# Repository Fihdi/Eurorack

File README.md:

# Open Source Eurorack Synthesizer

Schematics and PCBs for my Eurorack modules

**2nd May 2026: UNDER CONSTRUCTION!** I am currently fixing and re-organizing every module.

The following modules are being re-worked and can be found in their own repositories:

* 30hp Drum, Hi Hat and WAV Player: [MiniDrumkit](https://github.com/Fihdi/MiniDrumkit)
* 8hp ADSR Envelope Generator: [SCULPT](https://github.com/Fihdi/SCULPT)
* 8hp Dual VCAs / Ringmodulators: [BIPO](https://github.com/Fihdi/BIPO)
* 8hp 12dB/Oct State Variable VCF: [SVF12](https://github.com/Fihdi/SVF12)
* 8hp Voltage Controlled Attack/Release and Slew Rate limiter: [VCAR](https://github.com/Fihdi/VCAR)
* 8hp VCO/LFO: [UNO](https://github.com/Fihdi/UNO)
* 6hp S&H and Random Voltage/Gate generator: [DICE](https://github.com/Fihdi/DICE)
* 6hp Wavefolder: [MWMWM](https://github.com/Fihdi/MWMWM)
* 10hp Digital FX: [DSPFX](https://github.com/Fihdi/DSP-FX32)
* 8hp Four stage Phaser: [QPOL](https://github.com/Fihdi/QPOL)
* 10hp FM-Radio: [ATS20](https://github.com/Fihdi/ATS-20-Eurorack)
* 4hp Headphone/Line-Input: [LIN](https://github.com/Fihdi/LIN)

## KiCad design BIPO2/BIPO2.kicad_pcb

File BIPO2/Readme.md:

# 8hp Dual Bipolar VCA

BIPO (short for bipolar VCA) is a dual VCA and dual ring modulator (four quadrant multiplier). The VCA outputs are mixed together, so this module can acts as a 2 channel mixer or as a crossfader. This module serves as my general purpose VCA and as a replacement for my old crossfader module.

The four quadrant multiplication is achieved by taking an attenuverter topology and replacing the potentiometer with a VCA. The VCA needs to be biased in such a way that the amplitude of the VCA output is half of the input signal at 0V. The benefit of this topology is getting two outputs simultaneously

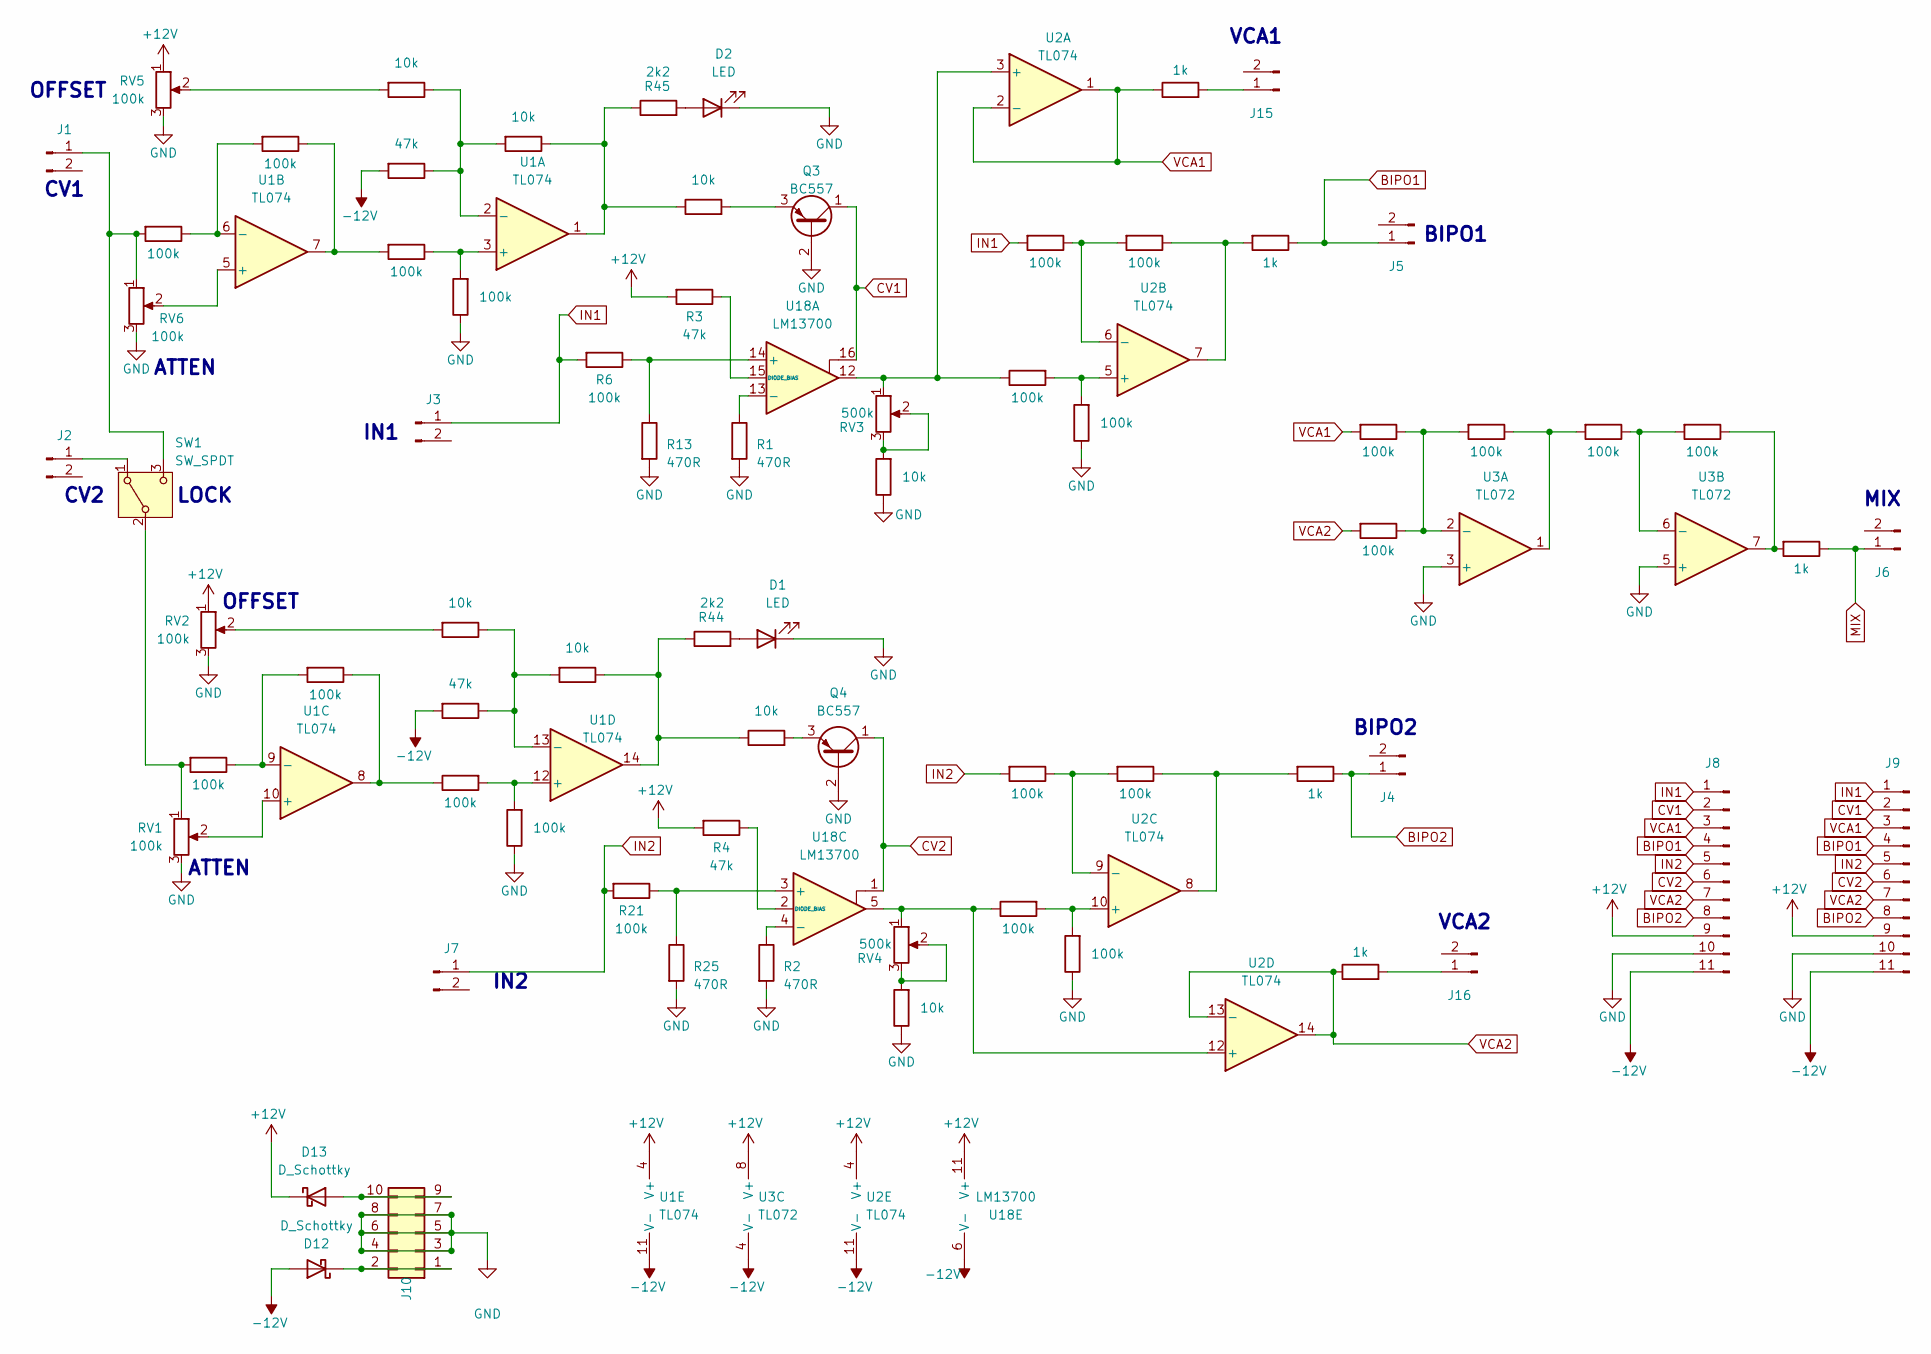
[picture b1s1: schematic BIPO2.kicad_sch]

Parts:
D1, D2: LED; LED_D3.0mm
D12, D13: D_Schottky; D_SOD-323_HandSoldering
J1, J2, J3, J4, J5, J6, J7, J15, J16: Conn_01x02_Pin; 3mm5 Mono Aux
J8, J9: Conn_01x11_Pin; PinHeader_1x11_P2.54mm_Vertical
J10: Conn_02x05_Odd_Even; IDC-Header_2x05_P2.54mm_Vertical
Q3, Q4: BC557; TO-92L_Inline_Wide
R1, R2, R13, R25: 470R; R_1206_3216Metric
R3, R4, R10, R22: 47k; R_1206_3216Metric
R5, R7, R11, R12, R20, R26, R28, R83: 10k; R_1206_3216Metric
R6, R8, R9, R14, R15, R16, R17, R18, R19, R21, R23, R24, R27, R29, R30, R31, R32, R34, R35, R38, R39, R41, R42: 100k; R_1206_3216Metric
R33, R36, R37, R40, R43: 1k; R_1206_3216Metric
R44, R45: 2k2; R_1206_3216Metric
RV1, RV2, RV5, RV6: 100k; AlpsPot_NoMountPins
RV3, RV4: 500k; Potentiometer_ACP_CA9-H5_Horizontal
SW1: SW_SPDT; Switch
U1, U2: TL074; SOIC-14_3.9x8.7mm_P1.27mm
U3: TL072; SOIC-8_3.9x4.9mm_P1.27mm
U18: LM13700; SOIC-16_3.9x9.9mm_P1.27mm

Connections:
+12V: D13.1 (K), J8.9, J9.9, R3.2, R4.2, RV2.1, RV5.1, U1.4 (V+), U2.4 (V+), U3.8 (V+), U18.11 (V+)
-12V: D12.2 (A), J8.11, J9.11, R10.2, R22.2, U1.11 (V-), U2.11 (V-), U3.4 (V-), U18.6 (V-)
BIPO1: J5.1, J8.4, J9.4, R36.1
BIPO2: J4.1, J8.8, J9.8, R33.1
CV1: J8.2, J9.2, Q3.1 (C), U18.16
CV2: J8.6, J9.6, Q4.1 (C), U18.1
GND: D1.1 (K), D2.1 (K), J8.10, J9.10, J10.3, J10.4, J10.5, J10.6, J10.7, J10.8, Q3.2 (B), Q4.2 (B), R1.2, R2.2, R5.1, R7.1, R8.1, R13.2, R24.1, R25.2, R39.1, R42.1, RV1.3, RV2.3, RV5.3, RV6.3, U3.3 (+), U3.5 (+)
IN1: J3.1, J8.1, J9.1, R6.2, R17.2
IN2: J7.1, J8.5, J9.5, R21.2, R34.2
MIX: J6.1, R37.1
unnamed: D1.2 (A), R44.2
unnamed: D2.2 (A), R45.2
unnamed: D12.1 (K), J10.1, J10.2
unnamed: D13.2 (A), J10.9, J10.10
unnamed: J1.1, R15.2, RV6.1, SW1.3 (C)
unnamed: J2.1, SW1.1 (A)
unnamed: J15.1, R40.2
unnamed: J16.1, R43.2
unnamed: Q3.3 (E), R83.2
unnamed: Q4.3 (E), R28.2
unnamed: R5.2, RV3.2, RV3.3
unnamed: R7.2, RV4.2, RV4.3
unnamed: R11.1, R45.1, R83.1, U1.1
unnamed: R12.2, RV5.2
unnamed: R9.2, R14.1, U1.7
unnamed: R16.1, R36.2, U2.7
unnamed: R19.1, R23.1, U1.8
unnamed: R20.2, RV2.2
unnamed: R26.1, R28.1, R44.1, U1.14
unnamed: R29.1, R30.2, U3.1
unnamed: R31.1, R37.2, U3.7
unnamed: R33.2, R35.1, U2.8
unnamed: R18.2, RV1.1, SW1.2 (B)
unnamed: R8.2, R9.1, U1.3 (+)
unnamed: R10.1, R11.2, R12.1, U1.2 (-)
unnamed: RV6.2, U1.5 (+)
unnamed: R14.2, R15.1, U1.6 (-)
unnamed: RV1.2, U1.10 (+)
unnamed: R18.1, R19.2, U1.9 (-)
unnamed: R23.2, R24.2, U1.12 (+)
unnamed: R20.1, R22.1, R26.2, U1.13 (-)
unnamed: R38.1, RV3.1, U2.3 (+), U18.12
unnamed: R38.2, R39.2, U2.5 (+)
unnamed: R16.2, R17.1, U2.6 (-)
unnamed: R41.2, R42.2, U2.10 (+)
unnamed: R34.1, R35.2, U2.9 (-)
unnamed: R41.1, RV4.1, U2.12 (+), U18.5
unnamed: R27.1, R29.2, R32.1, U3.2 (-)
unnamed: R30.1, R31.2, U3.6 (-)
unnamed: R6.1, R13.1, U18.14 (+)
unnamed: R1.1, U18.13 (-)
unnamed: R3.1, U18.15 (DIODE_BIAS)
unnamed: R21.1, R25.1, U18.3 (+)
unnamed: R2.1, U18.4 (-)
unnamed: R4.1, U18.2 (DIODE_BIAS)
VCA1: J8.3, J9.3, R27.2, R40.1, U2.1, U2.2 (-)
VCA2: J8.7, J9.7, R32.2, R43.1, U2.13 (-), U2.14

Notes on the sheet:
BIPO2
CV1
OFFSET
VCA1
IN2
LOCK
IN1
ATTEN
VCA2
BIPO1
MIX
CV2

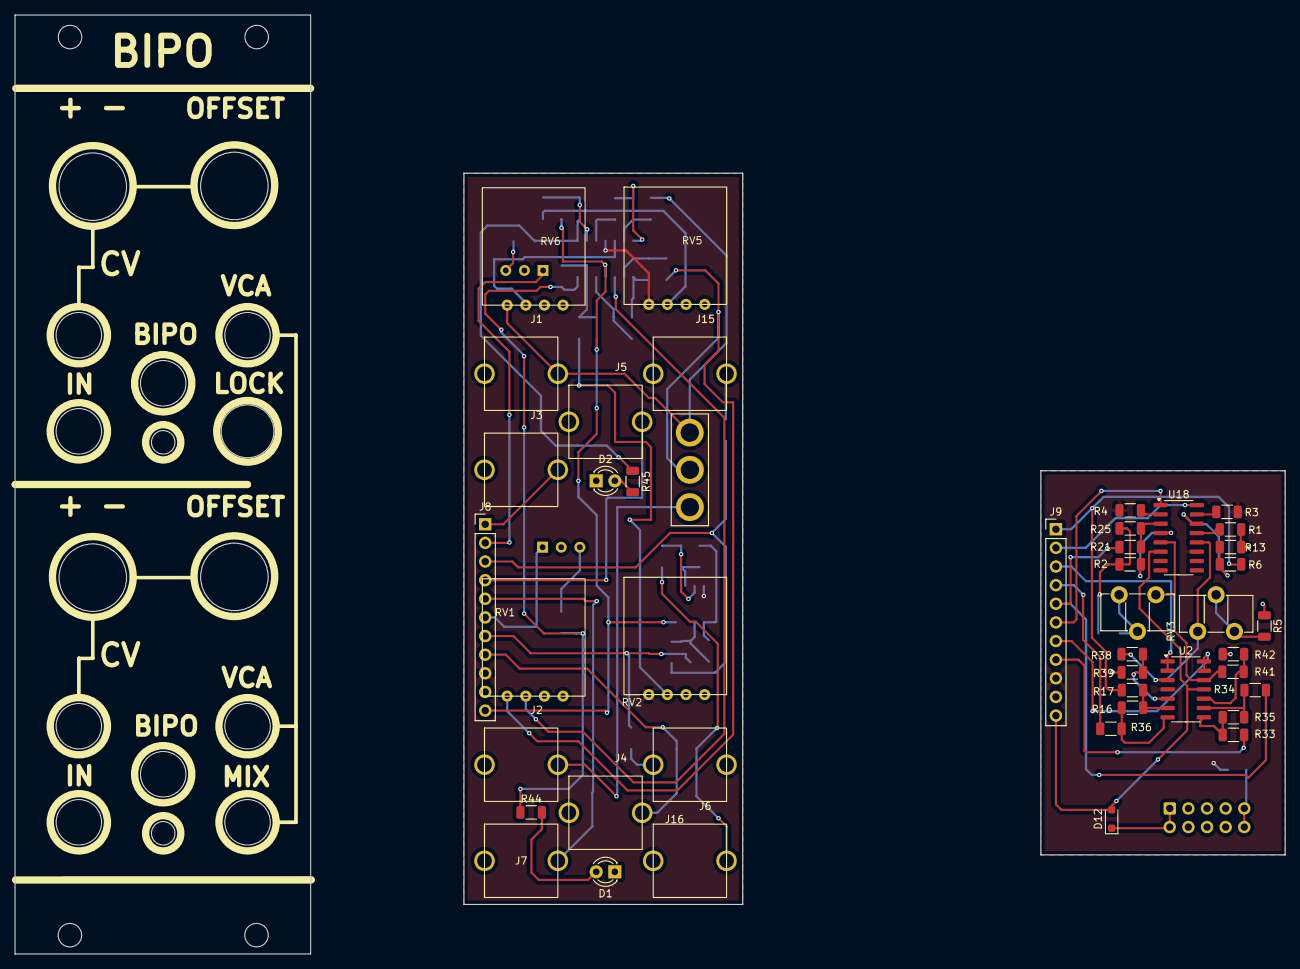
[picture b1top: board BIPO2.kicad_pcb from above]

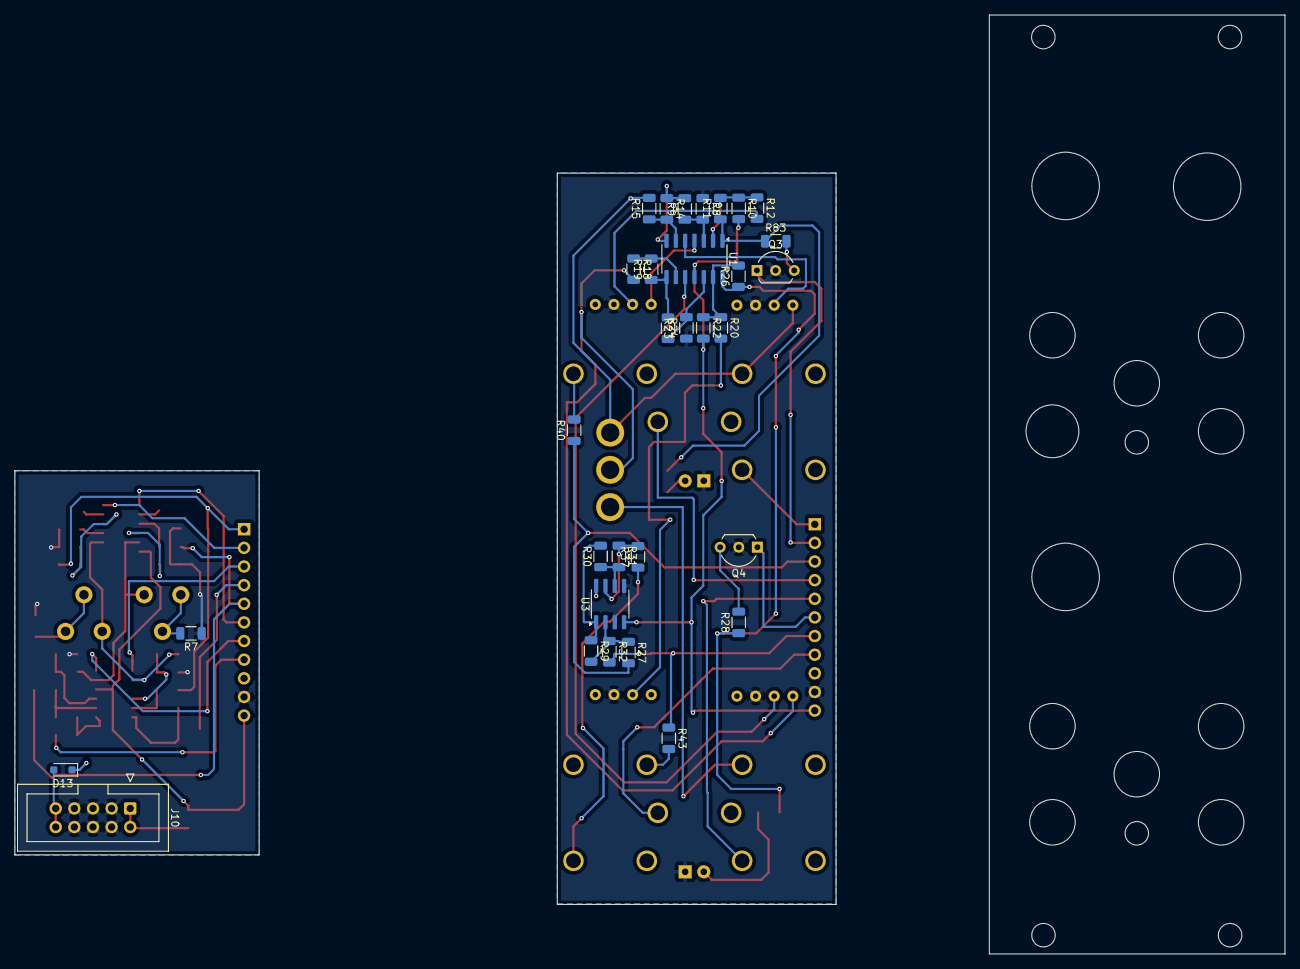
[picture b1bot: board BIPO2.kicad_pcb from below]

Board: 2 copper layers, 173.1 x 128.0 mm, 75 parts (31 on the bottom side), 57 nets.

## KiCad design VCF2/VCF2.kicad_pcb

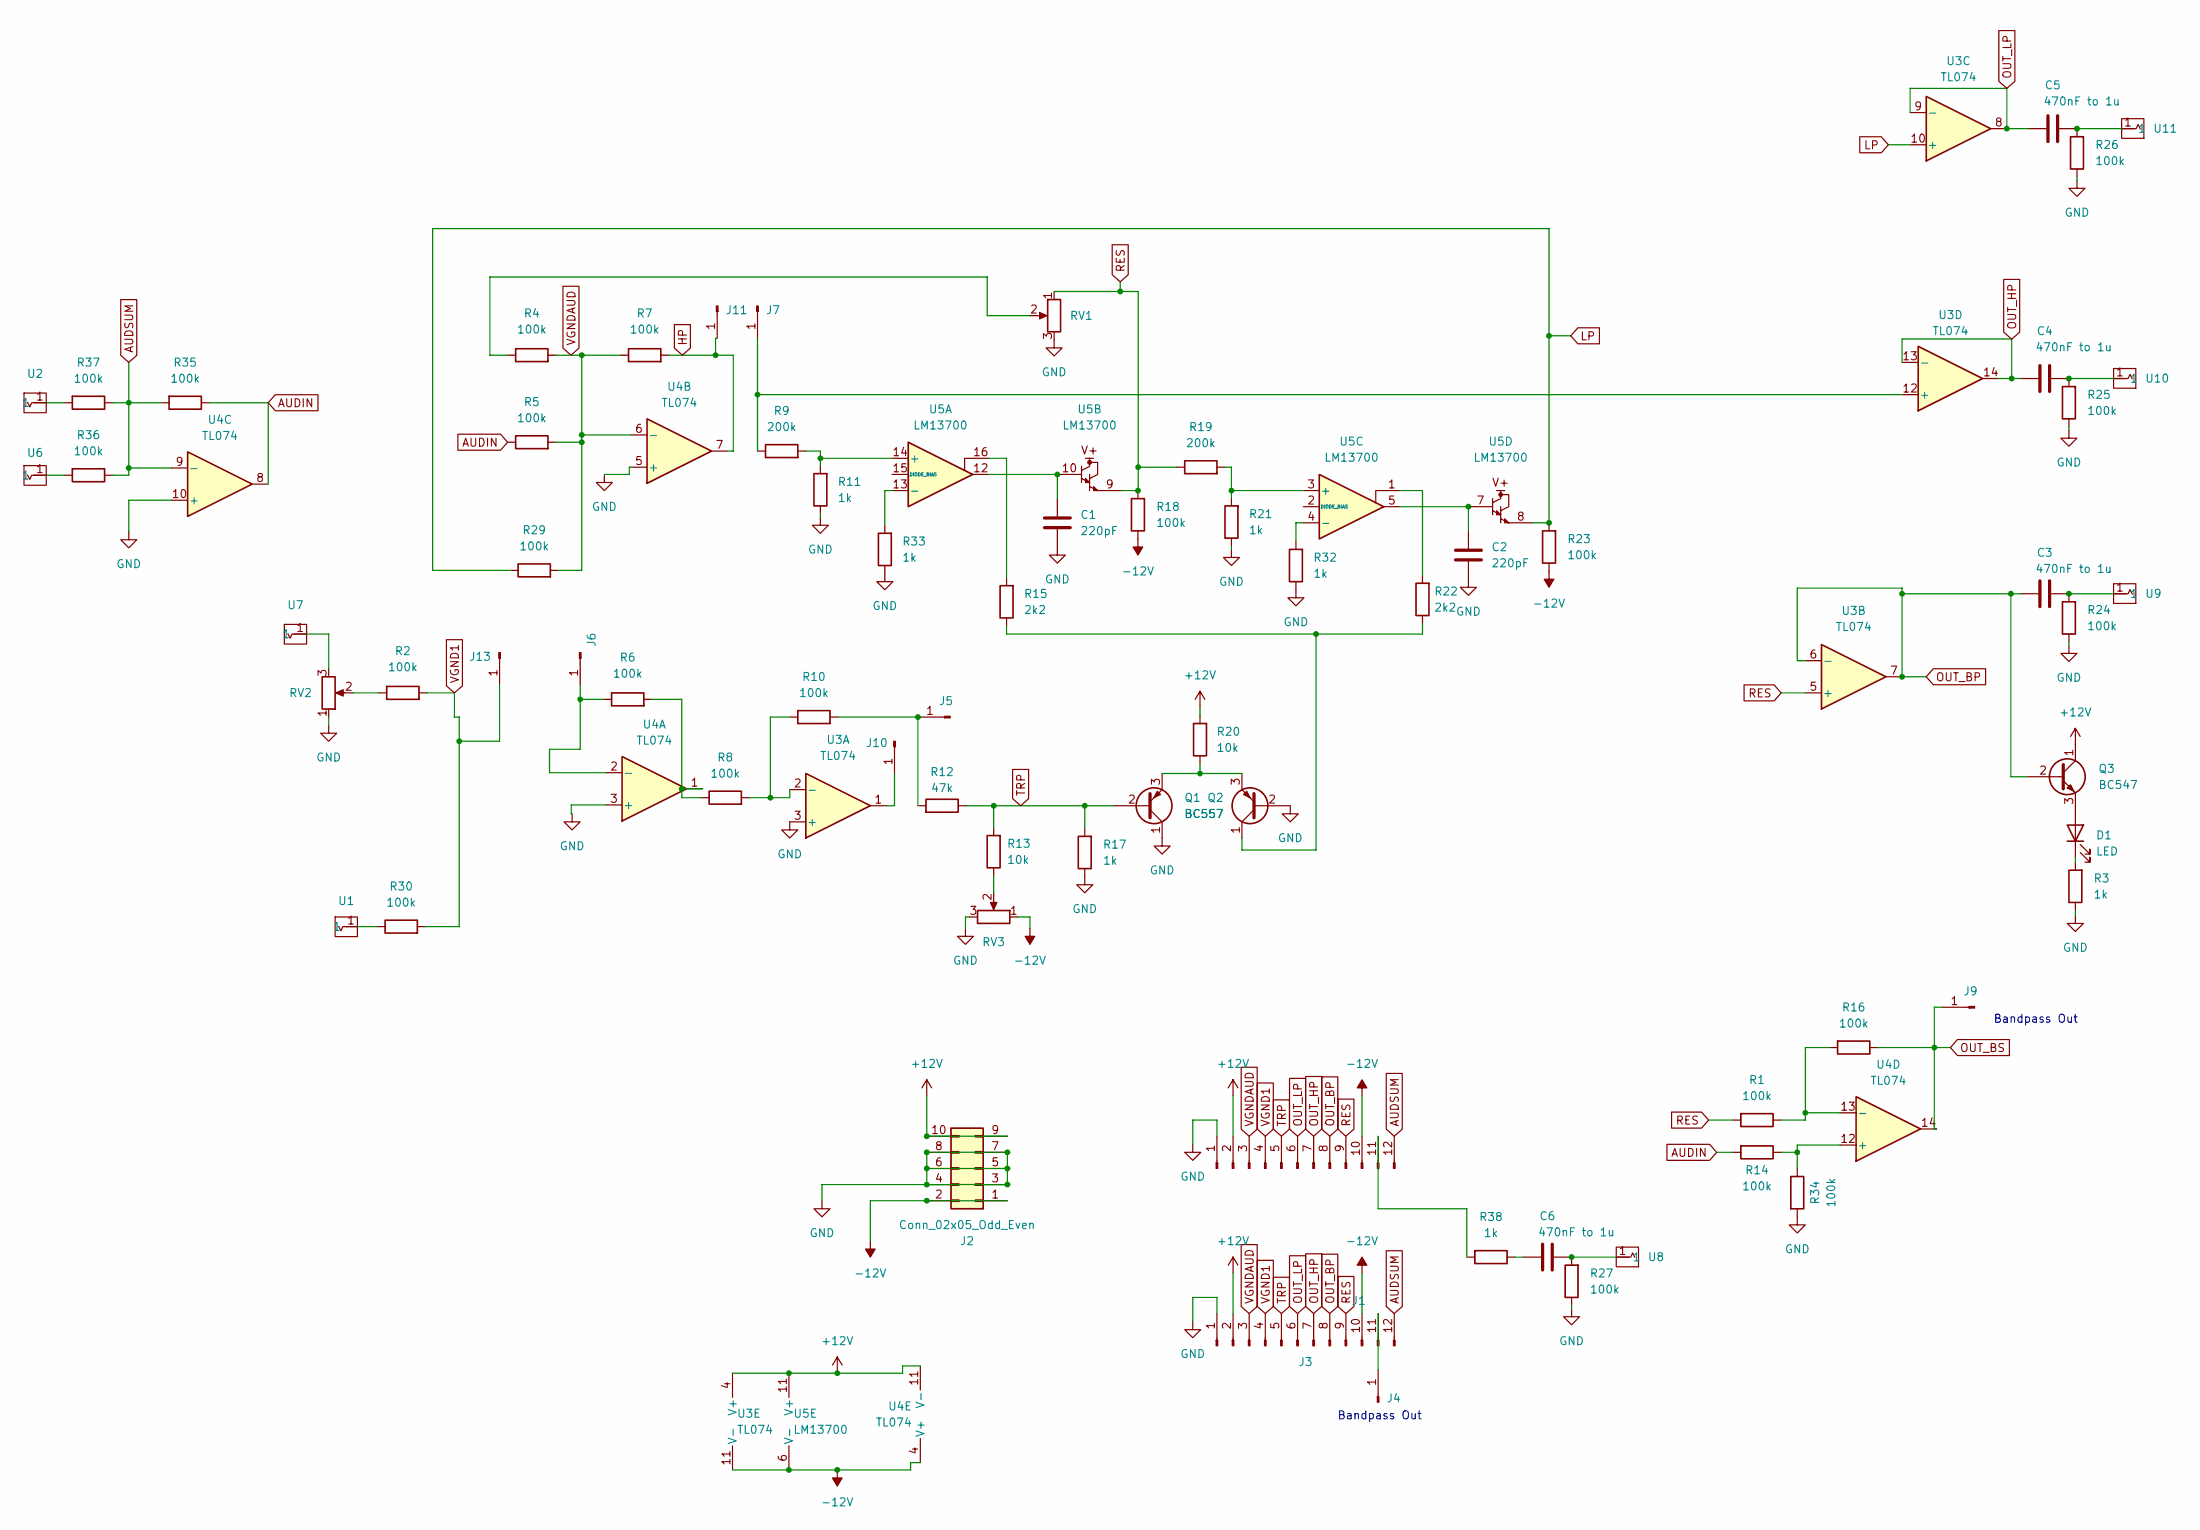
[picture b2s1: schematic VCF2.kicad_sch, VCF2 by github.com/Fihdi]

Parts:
C1, C2: 220pF; C_Disc_D7.0mm_W2.5mm_P5.00mm
C3, C4, C5: 470nF to 1u; C_Disc_D7.0mm_W2.5mm_P5.00mm
C6: 470nF to 1u; C_Disc_D9.0mm_W5.0mm_P5.00mm
D1: LED; LED_D3.0mm
J1, J3: Conn_01x12_Pin; PinHeader_1x12_P2.54mm_Vertical
J2: Conn_02x05_Odd_Even; PinHeader_2x05_P2.54mm_Vertical
J4, J5, J6, J7, J9, J10, J11, J13: Conn_01x01_Pin; PinHeader_1x01_P2.54mm_Vertical
Q1, Q2: BC557; TO-92_Inline_Wide
Q3: BC547; TO-92L_Inline_Wide
R1, R2, R4, R5, R6, R7, R8, R10, R14, R16, R18, R23, R24, R25, R26, R27, R29, R30, R34, R35, R36, R37: 100k; R_Axial_DIN0207_L6.3mm_D2.5mm_P7.62mm_Horizontal
R3, R11, R17, R21, R32, R33, R38: 1k; R_Axial_DIN0207_L6.3mm_D2.5mm_P7.62mm_Horizontal
R9, R19: 200k; R_Axial_DIN0207_L6.3mm_D2.5mm_P7.62mm_Horizontal
R12: 47k; R_Axial_DIN0207_L6.3mm_D2.5mm_P7.62mm_Horizontal
R13, R20: 10k; R_Axial_DIN0207_L6.3mm_D2.5mm_P7.62mm_Horizontal
R15, R22: 2k2; R_Axial_DIN0207_L6.3mm_D2.5mm_P7.62mm_Horizontal
RV1, RV2, RV3: R_Potentiometer; AlpsPot
U1, U2, U6, U7, U8, U9, U10, U11: Aux_flush; 3mm5 Mono Aux
U3, U4: TL074; DIP-14_W7.62mm
U5: LM13700; DIP-16_W7.62mm

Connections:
+12V: J1.2, J2.9, J2.10, J3.2, Q3.1 (C), R20.2, U3.4 (V+), U4.11 (V-), U5.11 (V+)
-12V: J1.10, J2.1, J2.2, J3.10, R18.1, R23.1, RV3.1, U3.11 (V-), U4.4 (V+), U5.6 (V-)
AUDIN: R5.1, R14.2, R35.1, U4.8
AUDSUM: J1.12, J3.12, R35.2, R36.1, R37.1, U4.9 (-)
GND: C1.2, C2.2, J1.1, J2.3, J2.4, J2.5, J2.6, J2.7, J2.8, J3.1, Q1.1 (C), Q2.2 (B), R3.1, R11.1, R17.1, R21.1, R24.1, R25.1, R26.1, R27.1, R32.1, R33.1, R34.2, RV1.3, RV2.1, RV3.3, U3.3 (+), U4.3 (+), U4.5 (+), U4.10 (+)
HP: J11.1, R7.2, U4.7
LP: R23.2, R29.1, U3.10 (+), U5.8
unnamed: C1.1, U5.10, U5.12
unnamed: C2.1, U5.5, U5.7
unnamed: C3.2, R24.2, U9.1
unnamed: C4.2, R25.2, U10.1
unnamed: C5.2, R26.2, U11.1
unnamed: C6.1, R38.1
unnamed: C6.2, R27.2, U8.1
unnamed: D1.2 (A), Q3.3 (E)
unnamed: D1.1 (K), R3.2
unnamed: J1.11, R38.2
unnamed: J3.11, J4.1
unnamed: J5.1, R10.2, R12.2
unnamed: J6.1, R6.1, U4.2 (-)
unnamed: J7.1, R9.1, U3.12 (+)
unnamed: J10.1, U3.1
unnamed: Q1.3 (E), Q2.3 (E), R20.1
unnamed: Q2.1 (C), R15.1, R22.1
unnamed: R2.1, RV2.2
unnamed: R4.1, RV1.2
unnamed: R6.2, R8.1, U4.1
unnamed: R13.1, RV3.2
unnamed: R15.2, U5.16
unnamed: R22.2, U5.1
unnamed: R30.1, U1.1
unnamed: R36.2, U6.1
unnamed: R37.2, U2.1
unnamed: RV2.3, U7.1
unnamed: R8.2, R10.1, U3.2 (-)
unnamed: R14.1, R34.1, U4.12 (+)
unnamed: R1.1, R16.2, U4.13 (-)
unnamed: R9.2, R11.2, U5.14 (+)
unnamed: R33.2, U5.13 (-)
unnamed: R19.2, R21.2, U5.3 (+)
unnamed: R32.2, U5.4 (-)
OUT_BP: C3.1, J1.8, J3.8, Q3.2 (B), U3.6 (-), U3.7
OUT_BS: J9.1, R16.1, U4.14
OUT_HP: C4.1, J1.7, J3.7, U3.13 (-), U3.14
OUT_LP: C5.1, J1.6, J3.6, U3.8, U3.9 (-)
RES: J1.9, J3.9, R1.2, R18.2, R19.1, RV1.1, U3.5 (+), U5.9
TRP: J1.5, J3.5, Q1.2 (B), R12.1, R13.2, R17.2
VGND1: J1.4, J3.4, J13.1, R2.2, R30.2
VGNDAUD: J1.3, J3.3, R4.2, R5.2, R7.1, R29.2, U4.6 (-)

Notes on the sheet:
Bandpass Out

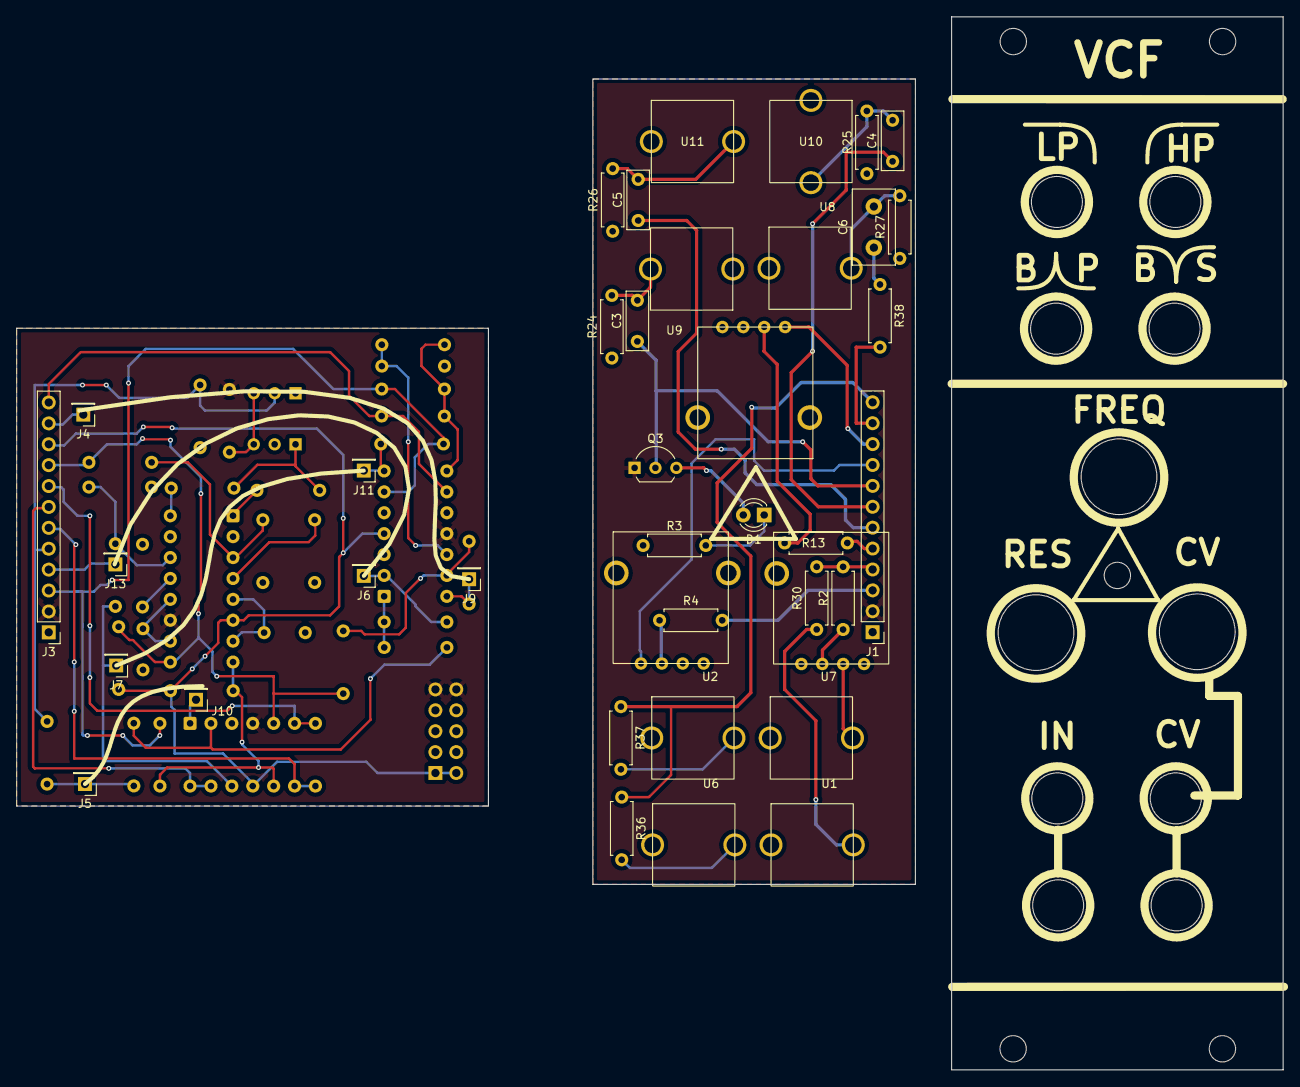
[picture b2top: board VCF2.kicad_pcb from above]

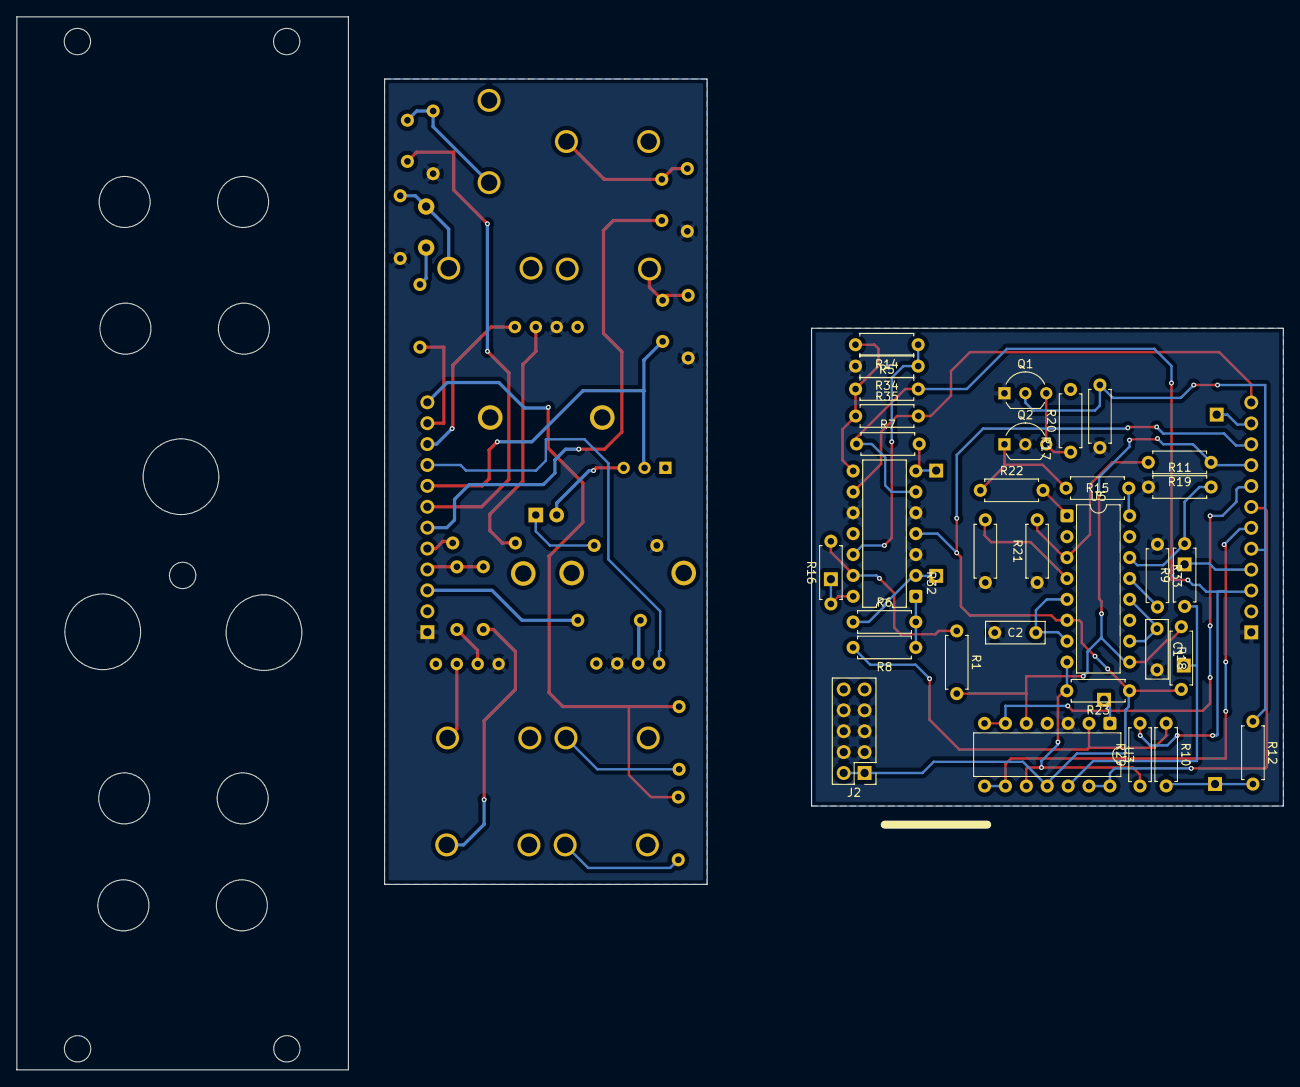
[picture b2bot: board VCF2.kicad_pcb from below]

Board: 2 copper layers, 153.9 x 128.0 mm, 71 parts (32 on the bottom side), 49 nets.

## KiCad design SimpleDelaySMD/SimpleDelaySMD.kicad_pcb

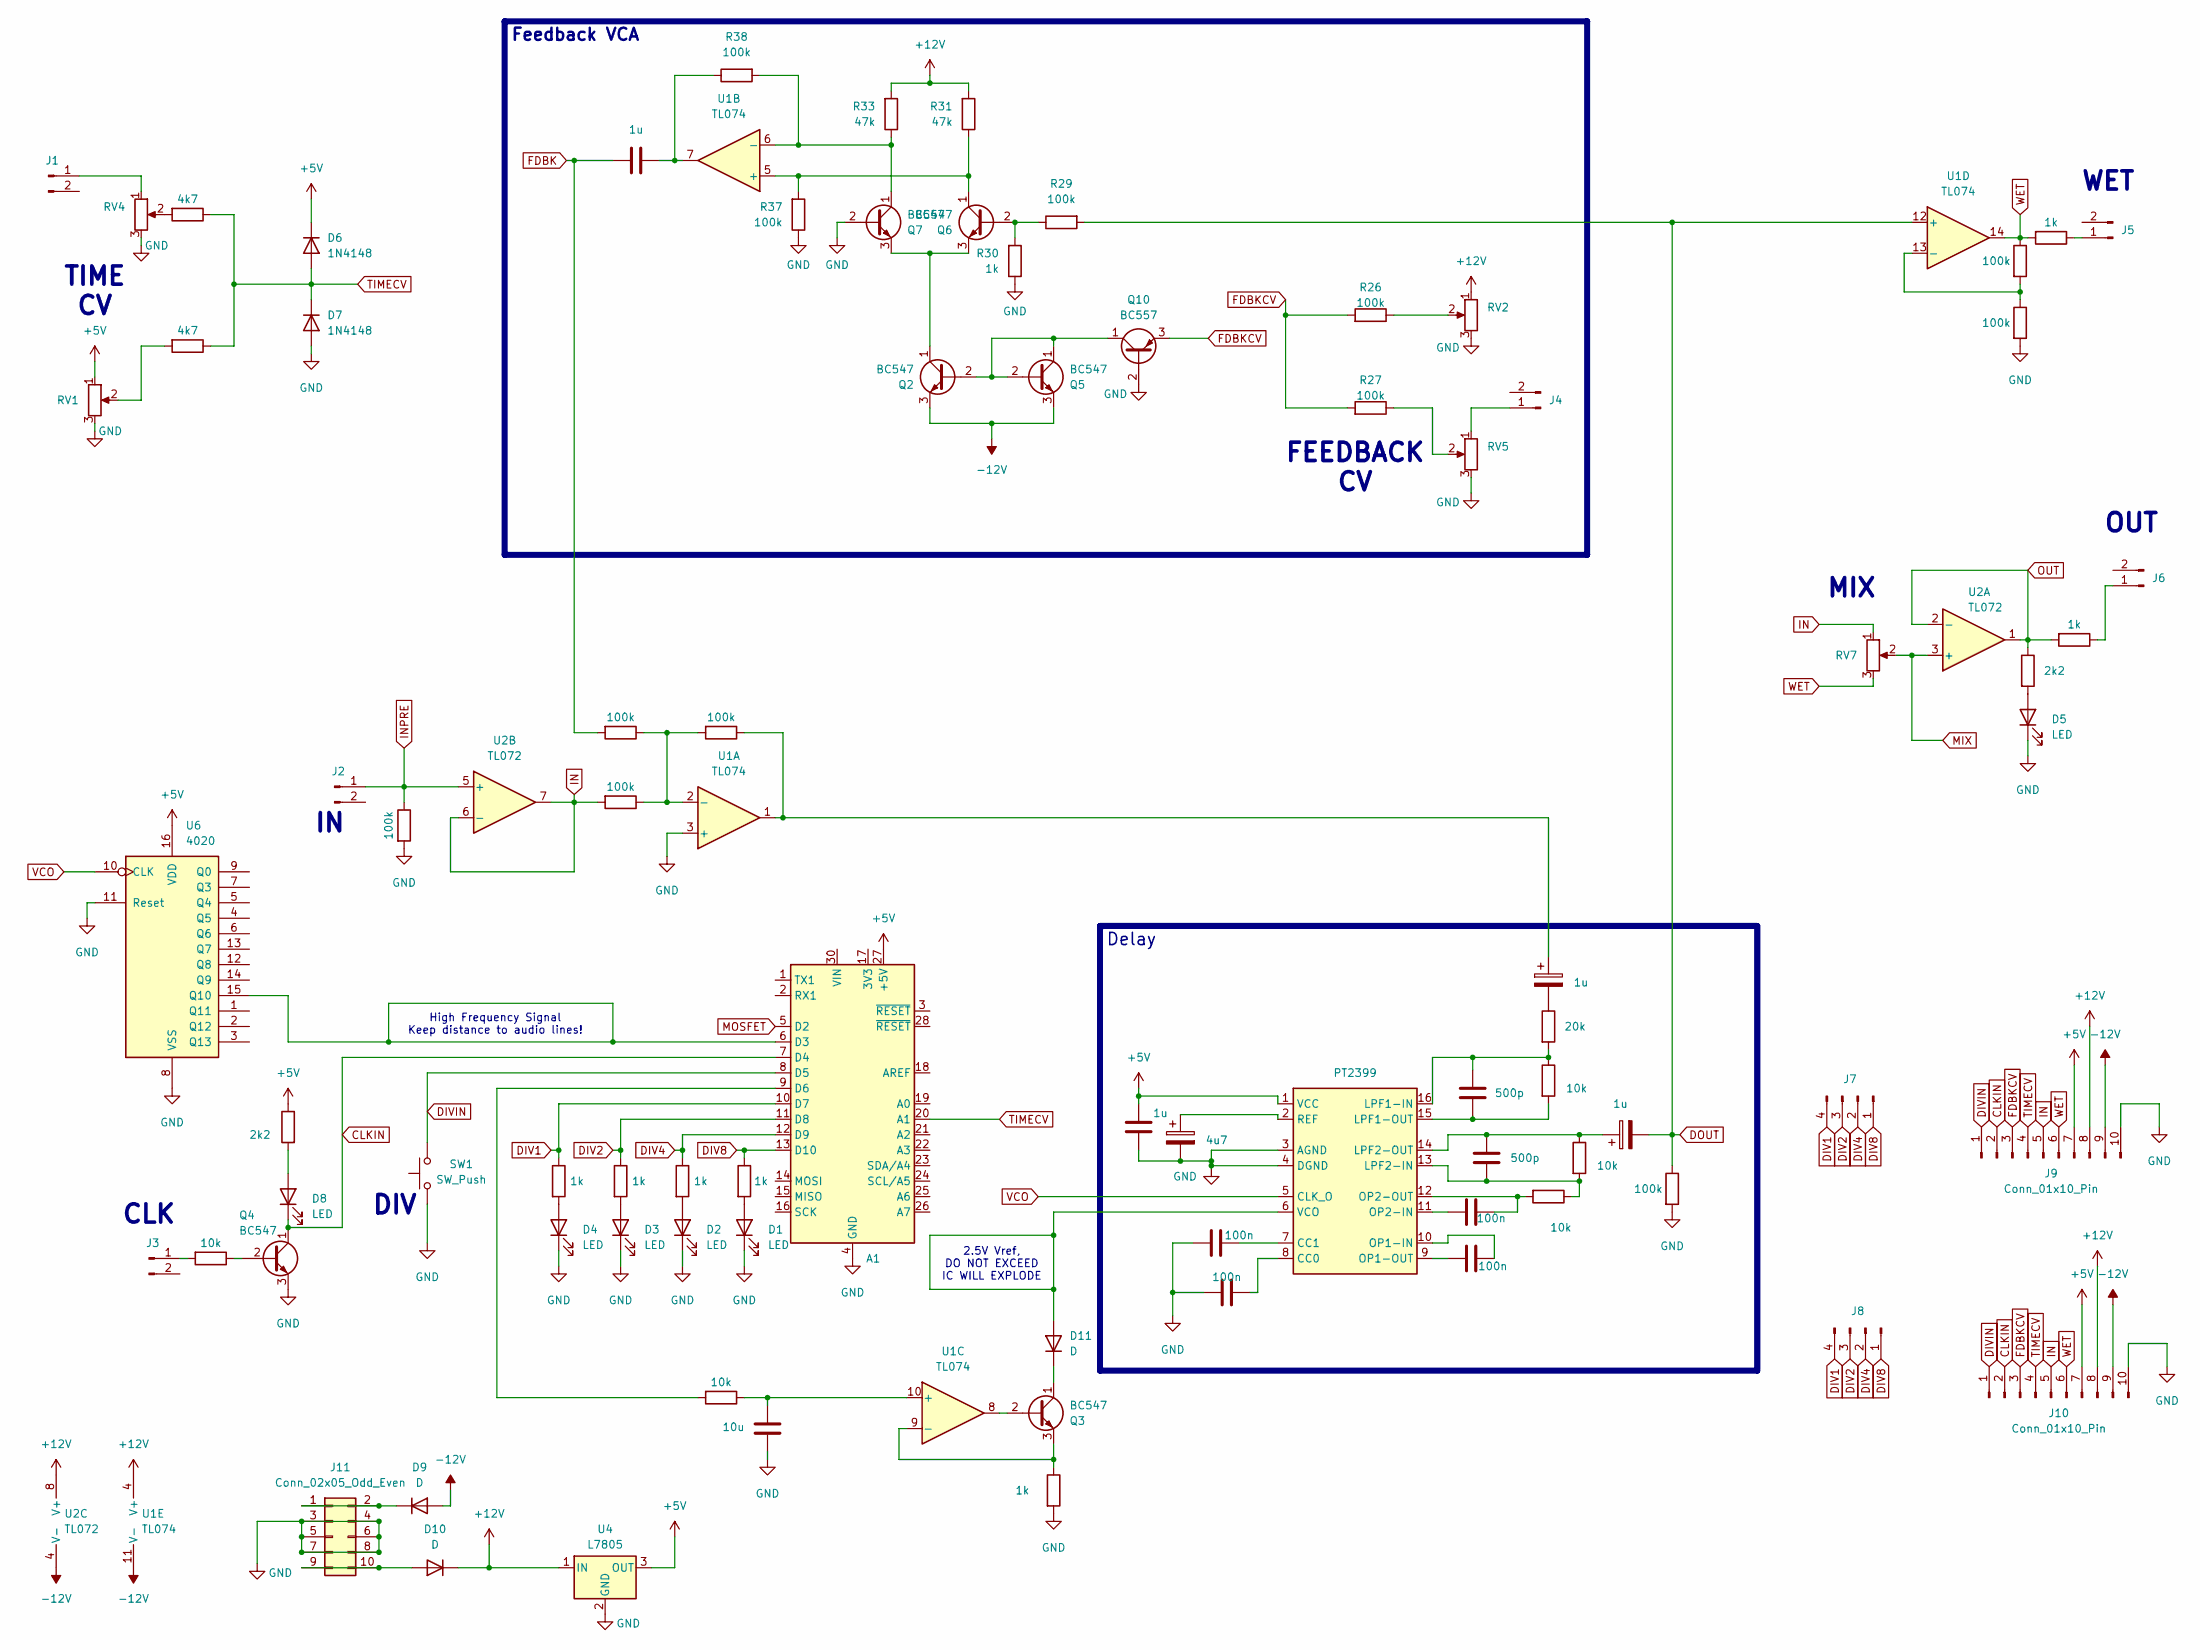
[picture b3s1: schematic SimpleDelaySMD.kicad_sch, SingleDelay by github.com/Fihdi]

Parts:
A1: Arduino_Nano_Every; Arduino_Nano
C1: 10u; C_Axial_L3.8mm_D2.6mm_P7.50mm_Horizontal
C9, C15: 1u; C_Axial_L3.8mm_D2.6mm_P7.50mm_Horizontal
C16: 4u7; C_Rect_L9.0mm_W2.7mm_P7.50mm_MKT
C17, C18, C20, C22: 100n; C_Disc_D4.7mm_W2.5mm_P5.00mm
C21, C23: 500p; C_Disc_D4.7mm_W2.5mm_P5.00mm
C24, C25: 1u; C_Rect_L9.0mm_W2.7mm_P7.50mm_MKT
D1, D2, D3, D4, D5, D8: LED; LED_D3.0mm
D6, D7: 1N4148; D_DO-35_SOD27_P7.62mm_Horizontal
D9, D10, D11: D; D_1206_3216Metric_Pad1.42x1.75mm_HandSolder
J1, J2, J3, J4, J5, J6: Conn_01x02_Pin; 3mm5 Mono Aux
J7, J8: Conn_01x04_Pin; PinHeader_1x04_P2.54mm_Vertical
J9, J10: Conn_01x10_Pin; PinHeader_1x10_P2.54mm_Vertical
J11: Conn_02x05_Odd_Even; IDC-Header_2x05_P2.54mm_Vertical
Q2, Q3, Q4, Q5, Q6, Q7: BC547; TO-92L_Inline_Wide
Q10: BC557; TO-92L_Inline_Wide
R1, R4, R5, R6, R7, R10, R15, R30: 1k; R_1206_3216Metric
R2, R3, R12, R13, R22, R23, R24, R26, R27, R29, R37, R38: 100k; R_1206_3216Metric
R8, R20, R32, R35, R36: 10k; R_1206_3216Metric
R11, R21: 2k2; R_1206_3216Metric
R25, R28: 4k7; R_1206_3216Metric
R31, R33: 47k; R_1206_3216Metric
R34: 20k; R_1206_3216Metric
RV1, RV2, RV4, RV5: R_Potentiometer; AlpsPot
RV7: 100k; AlpsPot
SW1: SW_Push; PushButton
U1: TL074; SOIC-14_3.9x8.7mm_P1.27mm
U2: TL072; SOIC-8_5.3x6.2mm_P1.27mm
U4: L7805; TO-252-3_TabPin2
U6: 4020; SOP-16_4.4x10.4mm_P1.27mm
U9: PT2399; DIP-16_W7.62mm

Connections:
+5V: A1.27 (+5V), C15.1, D6.1 (K), J9.7, J10.7, R21.1, RV1.1, U4.3 (OUT), U6.16 (VDD), U9.1 (VCC)
+12V: D10.1 (K), J9.8, J10.8, R31.2, R33.2, RV2.1, U1.4 (V+), U2.8 (V+), U4.1 (IN)
-12V: D9.2 (A), J9.9, J10.9, Q2.3 (E), Q5.3 (E), U1.11 (V-), U2.4 (V-)
CLKIN: A1.7 (D4), D8.1 (K), J9.2, J10.2, Q4.1 (C)
DIV1: A1.10 (D7), J7.4, J8.4, R7.1
DIV2: A1.11 (D8), J7.3, J8.3, R6.1
DIV4: A1.12 (D9), J7.2, J8.2, R5.1
DIV8: A1.13 (D10), J7.1, J8.1, R4.1
DIVIN: A1.8 (D5), J9.1, J10.1, SW1.2
DOUT: C25.2, R12.1, R29.2, U1.12 (+)
FDBK: C9.1, R24.2
FDBKCV: J9.3, J10.3, Q10.3 (E), R26.2, R27.2
GND: A1.4 (GND), A1.29 (GND), C1.1, C15.2, C16.2, C17.1, C18.1, D1.1 (K), D2.1 (K), D3.1 (K), D4.1 (K), D5.1 (K), D7.2 (A), J9.10, J10.10, J11.3, J11.4, J11.5, J11.6, J11.7, J11.8, Q4.3 (E), Q7.2 (B), Q10.2 (B), R2.2, R10.2, R12.2, R13.2, R30.1, R37.1, RV1.3, RV2.3, RV4.3, RV5.3, SW1.1, U1.3 (+), U4.2 (GND), U6.8 (VSS), U6.11 (Reset), U9.3 (AGND), U9.4 (DGND)
IN: J9.5, J10.5, R22.2, RV7.1, U2.6 (-), U2.7
INPRE: J2.1, R13.1, U2.5 (+)
MIX: RV7.2, U2.3 (+)
MOSFET: A1.5 (D2)
unnamed: A1.6 (D3), U6.15 (Q10)
unnamed: A1.9 (D6), R8.2
unnamed: C9.2, R38.1, U1.7
unnamed: C24.1, R23.1, U1.1
unnamed: C24.2, R34.1
unnamed: D1.2 (A), R4.2
unnamed: D2.2 (A), R5.2
unnamed: D3.2 (A), R6.2
unnamed: D4.2 (A), R7.2
unnamed: D5.2 (A), R11.2
unnamed: D8.2 (A), R21.2
unnamed: D9.1 (K), J11.1, J11.2
unnamed: D10.2 (A), J11.9, J11.10
unnamed: D11.2 (A), U9.6 (VCO)
unnamed: D11.1 (K), Q3.1 (C)
unnamed: J1.1, RV4.1
unnamed: J3.1, R20.2
unnamed: J4.1, RV5.1
unnamed: J5.1, R1.1
unnamed: J6.1, R15.1
unnamed: Q2.1 (C), Q6.3 (E), Q7.3 (E)
unnamed: Q3.2 (B), U1.8
unnamed: Q3.3 (E), R10.1, U1.9 (-)
unnamed: Q4.2 (B), R20.1
unnamed: Q6.2 (B), R29.1, R30.2
unnamed: Q6.1 (C), R31.1, R37.2, U1.5 (+)
unnamed: Q7.1 (C), R33.1, R38.2, U1.6 (-)
unnamed: Q2.2 (B), Q5.1 (C), Q5.2 (B), Q10.1 (C)
unnamed: R25.2, RV4.2
unnamed: R26.1, RV2.2
unnamed: R27.1, RV5.2
unnamed: R28.2, RV1.2
unnamed: R22.1, R23.2, R24.1, U1.2 (-)
unnamed: C1.2, R8.1, U1.10 (+)
unnamed: R2.1, R3.2, U1.13 (-)
unnamed: C18.2, U9.8 (CC0)
unnamed: C17.2, U9.7 (CC1)
unnamed: C21.1, R34.2, R35.1, U9.16 (LPF1-IN)
unnamed: C21.2, R35.2, U9.15 (LPF1-OUT)
unnamed: C23.2, R32.1, R36.2, U9.13 (LPF2-IN)
unnamed: C23.1, C25.1, R36.1, U9.14 (LPF2-OUT)
unnamed: C20.2, U9.10 (OP1-IN)
unnamed: C20.1, U9.9 (OP1-OUT)
unnamed: C22.1, U9.11 (OP2-IN)
unnamed: C22.2, R32.2, U9.12 (OP2-OUT)
unnamed: C16.1, U9.2 (REF)
OUT: R11.1, R15.2, U2.1, U2.2 (-)
TIMECV: A1.20 (A1), D6.2 (A), D7.1 (K), J9.4, J10.4, R25.1, R28.1
VCO: U6.10 (CLK), U9.5 (CLK_O)
WET: J9.6, J10.6, R1.2, R3.1, RV7.3, U1.14

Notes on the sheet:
MIX
TIME CV
High Frequency Signal Keep distance to audio lines!
WET
DIV
2.5V Vref, DO NOT EXCEED IC WILL EXPLODE
CLK
FEEDBACK CV
OUT
Delay
Feedback VCA
